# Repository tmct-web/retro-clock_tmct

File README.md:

# retro-clock_tmct
All discrete logic clock

This is a clock made by combining only logic ICs, so-called DIP components, without using a microcontroller.  
KiCad project files are available.

You can find more information on the following page. (*Japanese only)

[tmct web-site:nixie-clock](https://ss1.xrea.com/tmct.s1009.xrea.com/work/td-ja-7e4l01.html)

---
マイコンを使わず、いわゆるDIP部品のロジックICだけを組み合わせて作った時計です。  
KiCadのプロジェクトファイル一式を公開しています。

設計の仕様・組み立て方などの詳細は下記のページをご覧ください。

[tmct web-site:nixie-clock](https://ss1.xrea.com/tmct.s1009.xrea.com/work/td-ja-7e4l01.html)

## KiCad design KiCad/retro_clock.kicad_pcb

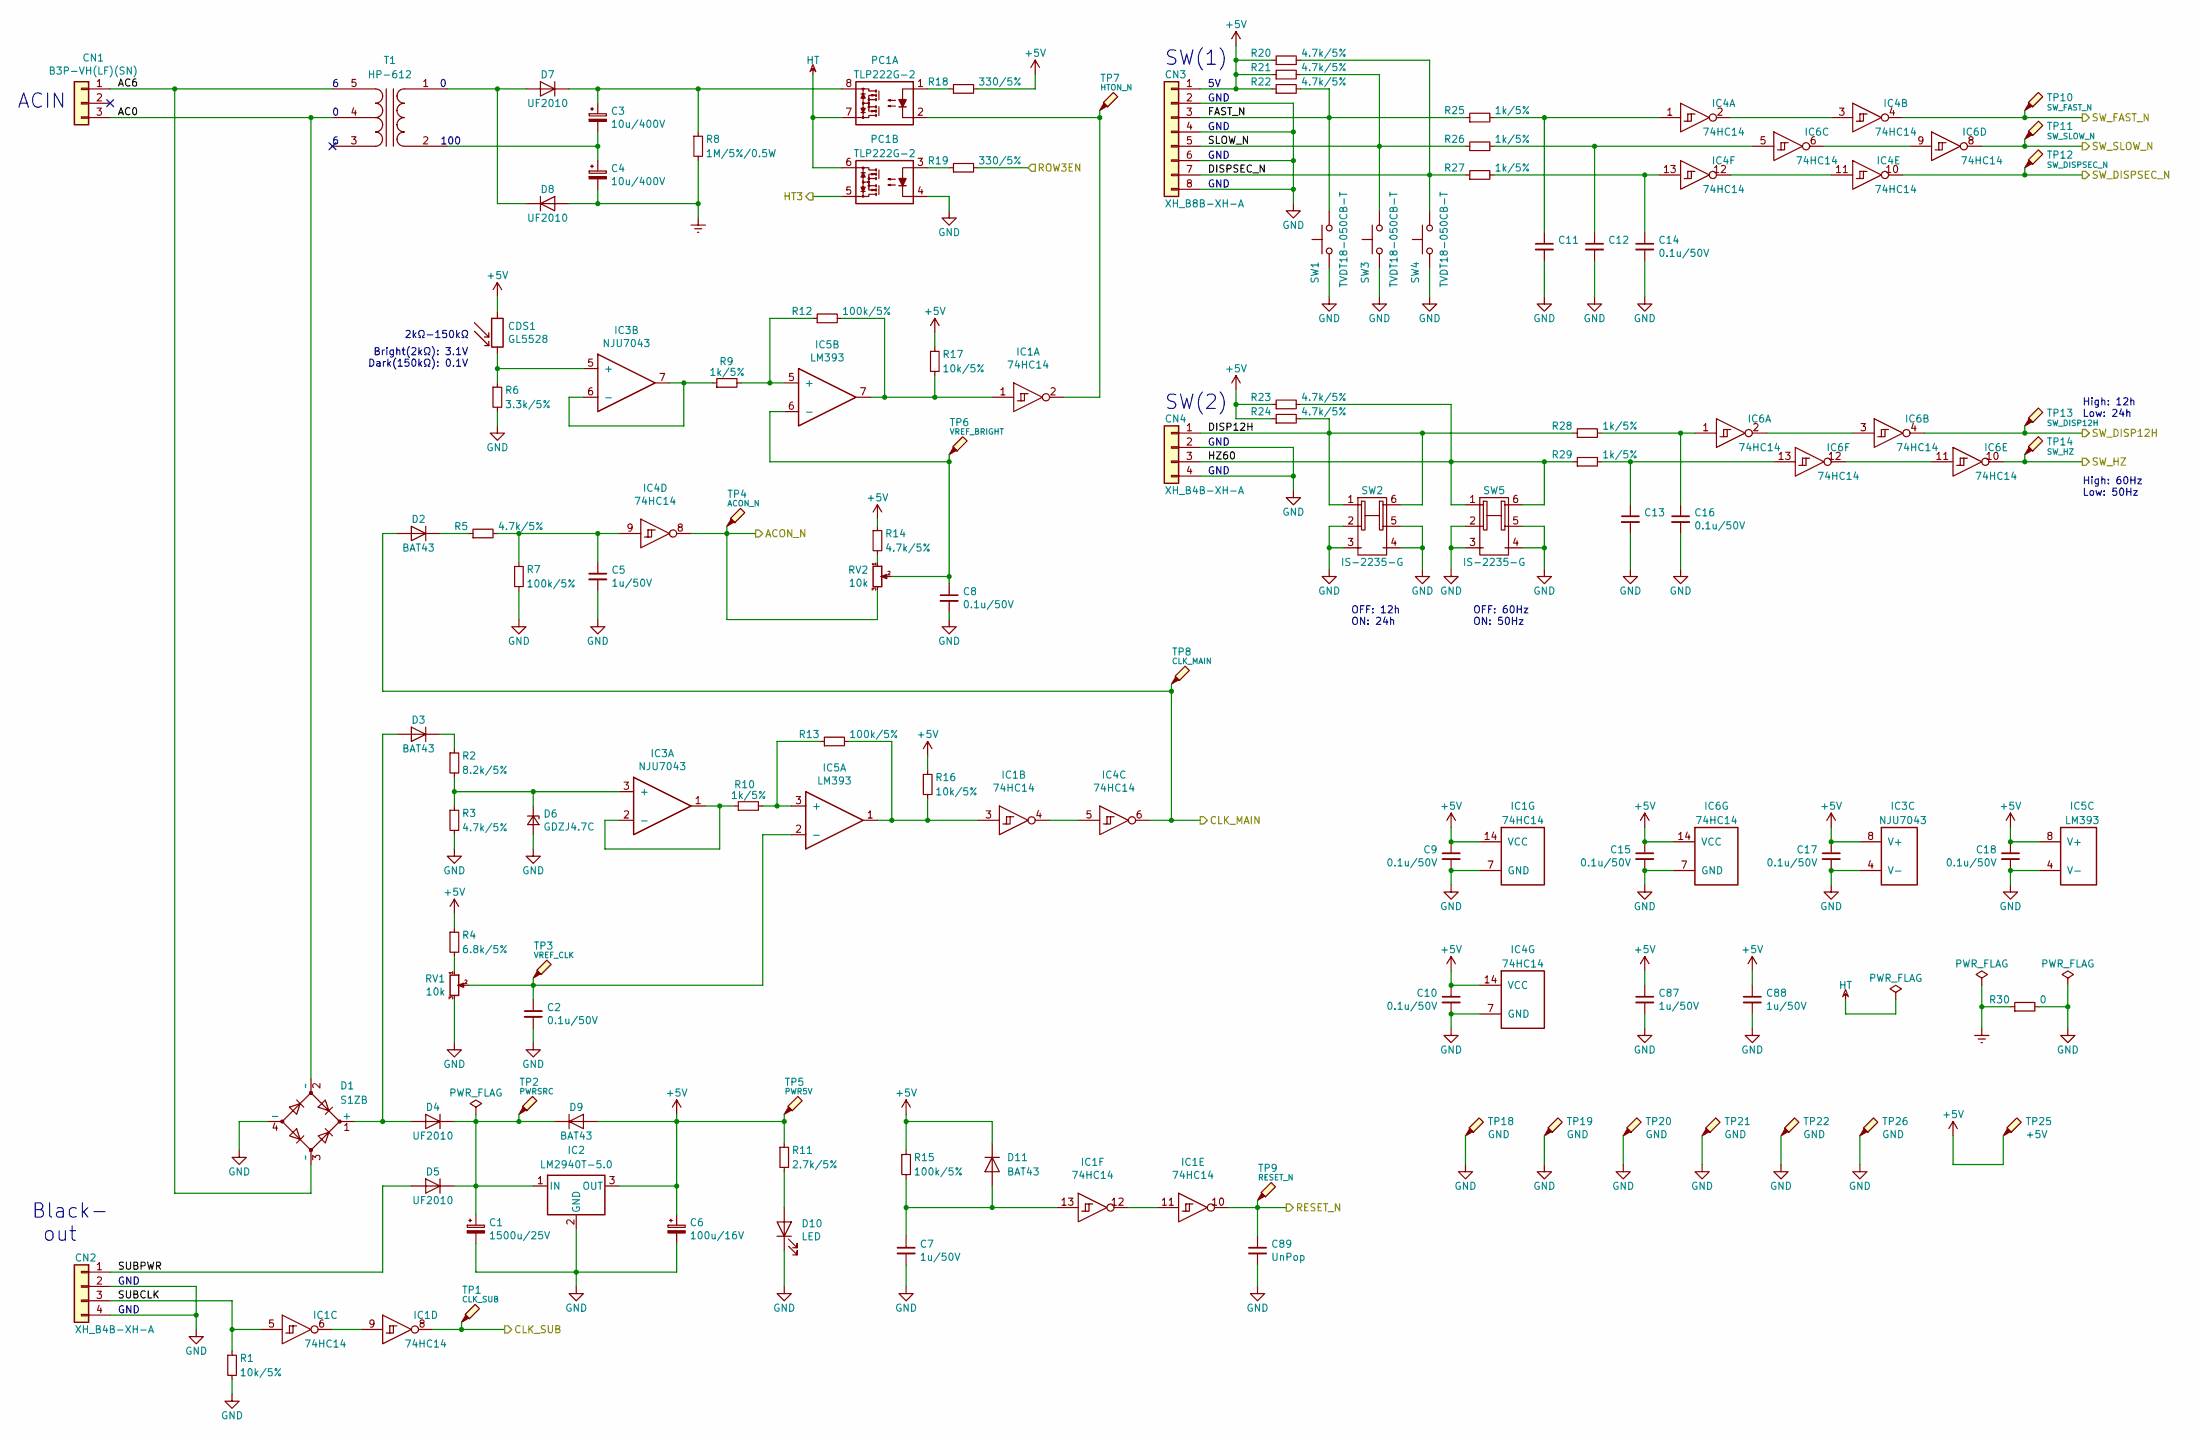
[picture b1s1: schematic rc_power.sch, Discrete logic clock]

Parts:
C1: 1500u/25V; CP_Radial_D12.5mm_P5.00mm
C2, C8, C9, C10, C11, C12, C13, C14, C15, C16, C17, C18: 0.1u/50V; C_Disc_P2.50mm
C3, C4: 10u/400V; CP_Radial_D12.5mm_P5.00mm
C5, C7, C87, C88: 1u/50V; C_Disc_P2.50mm
C6: 100u/16V; CP_Radial_D5.0mm_P2.00mm
C89: UnPop; C_Disc_P2.50mm
CDS1: GL5528; R_CDS_5.1x4.3mm_P3.4mm_Vertical
CN1: B3P-VH(LF)(SN); JST_VH_B3P-VH-B_1x03_P3.96mm_Vertical
CN2, CN4: XH_B4B-XH-A; JST_XH_B4B-XH-A_1x04_P2.50mm_Vertical
CN3: XH_B8B-XH-A; JST_XH_B8B-XH-A_1x08_P2.50mm_Vertical
D1: S1ZB; S1ZB-THD
D2, D3, D9, D11: BAT43; D_A-405_P7.62mm_Horizontal
D4, D5, D7, D8: UF2010; D_A-405_P10.16mm_Horizontal
D6: GDZJ4.7C; D_A-405_P7.62mm_Horizontal
D10: LED; LED_D3.0mm
IC1, IC4, IC6: 74HC14; DIP-14_W7.62mm_Socket_LongPads
IC2: LM2940T-5.0; TO-220-3_Vertical
IC3: NJU7043; DIP-8_W7.62mm_Socket_LongPads
IC5: LM393; DIP-8_W7.62mm_Socket_LongPads
PC1: TLP222G-2; DIP-8_W7.62mm_Socket_LongPads
R1, R16, R17: 10k/5%; R_Axial_P5.08mm_Horizontal
R2: 8.2k/5%; R_Axial_P5.08mm_Horizontal
R3, R5, R14, R20, R21, R22, R23, R24: 4.7k/5%; R_Axial_P5.08mm_Horizontal
R4: 6.8k/5%; R_Axial_P5.08mm_Horizontal
R6: 3.3k/5%; R_Axial_P5.08mm_Horizontal
R7, R12, R13, R15: 100k/5%; R_Axial_P5.08mm_Horizontal
R8: 1M/5%/0.5W; R_Axial_P7.62mm_Horizontal
R9, R10, R25, R26, R27, R28, R29: 1k/5%; R_Axial_P5.08mm_Horizontal
R11: 2.7k/5%; R_Axial_P5.08mm_Horizontal
R18, R19: 330/5%; R_Axial_P5.08mm_Horizontal
R30: 0; R_Axial_P5.08mm_Horizontal
RV1, RV2: 10k; Potentiometer_Bourns_3296W_Vertical
SW1, SW3, SW4: TVDT18-050CB-T
SW2, SW5: IS-2235-G
T1: HP-612; HP-098
TP1: CLK_SUB; TestPoint_THTPad_1.5x1.5mm_Drill0.7mm
TP2: PWRSRC; TestPoint_THTPad_1.5x1.5mm_Drill0.7mm
TP3: VREF_CLK; TestPoint_THTPad_1.5x1.5mm_Drill0.7mm
TP4: ACON_N; TestPoint_THTPad_1.5x1.5mm_Drill0.7mm
TP5: PWR5V; TestPoint_THTPad_1.5x1.5mm_Drill0.7mm
TP6: VREF_BRIGHT; TestPoint_THTPad_1.5x1.5mm_Drill0.7mm
TP7: HTON_N; TestPoint_THTPad_1.5x1.5mm_Drill0.7mm
TP8: CLK_MAIN; TestPoint_THTPad_1.5x1.5mm_Drill0.7mm
TP9: RESET_N; TestPoint_THTPad_1.5x1.5mm_Drill0.7mm
TP10: SW_FAST_N; TestPoint_THTPad_1.5x1.5mm_Drill0.7mm
TP11: SW_SLOW_N; TestPoint_THTPad_1.5x1.5mm_Drill0.7mm
TP12: SW_DISPSEC_N; TestPoint_THTPad_1.5x1.5mm_Drill0.7mm
TP13: SW_DISP12H; TestPoint_THTPad_1.5x1.5mm_Drill0.7mm
TP14: SW_HZ; TestPoint_THTPad_1.5x1.5mm_Drill0.7mm
TP18, TP19, TP20, TP21, TP22, TP26: GND; TestPoint_Loop_D2.60mm_Drill0.9mm_Beaded
TP25: +5V; TestPoint_Loop_D2.60mm_Drill0.9mm_Beaded

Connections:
+5V: C6.1, C9.1, C10.1, C15.1, C17.1, C18.1, C87.1, C88.1, CDS1.1, CN3.1, D9.2 (A), D11.1 (K), IC1.14 (VCC), IC2.3 (OUT), IC3.8 (V+), IC4.14 (VCC), IC5.8 (V+), IC6.14 (VCC), R4.1, R11.1, R14.1, R15.1, R16.1, R17.1, R18.2, R20.1, R21.1, R22.1, R23.1, R24.1, TP5.1, TP25.1; also elsewhere on the board
/Display block/HT3: PC1.5; also elsewhere on the board
/Divider block/ACON_N: IC4.8, RV2.3, TP4.1; also elsewhere on the board
/Divider block/CLK_MAIN: D2.2 (A), IC4.6, TP8.1; also elsewhere on the board
/Divider block/CLK_SUB: IC1.8, TP1.1; also elsewhere on the board
/Divider block/RESET_N: C89.1, IC1.10, TP9.1; also elsewhere on the board
/Divider block/SW_DISP12H: IC6.4, TP13.1; also elsewhere on the board
/Divider block/SW_DISPSEC_N: IC4.10, TP12.1; also elsewhere on the board
/Divider block/SW_FAST_N: IC4.4, TP10.1; also elsewhere on the board
/Divider block/SW_HZ: IC6.10, TP14.1; also elsewhere on the board
/Divider block/SW_SLOW_N: IC6.8, TP11.1; also elsewhere on the board
/Driver block/ROW3EN: R19.2; also elsewhere on the board
/Power block/AC0: CN1.3, D1.2 (~~), T1.4 (SC)
/Power block/AC6: CN1.1, D1.3 (~~), T1.5 (SB)
/Power block/DISP12H: CN4.1, R24.2, R28.1, SW2.1 (1a), SW2.6 (2a)
/Power block/DISPSEC_N: CN3.7, R20.2, R27.1, SW4.2
/Power block/FAST_N: CN3.3, R22.2, R25.1, SW1.2
/Power block/HZ60: CN4.3, R23.2, R29.1, SW5.1 (1a), SW5.6 (2a)
/Power block/SLOW_N: CN3.5, R21.2, R26.1, SW3.2
/Power block/SUBCLK: CN2.3, IC1.5, R1.1
/Power block/SUBPWR: CN2.1, D5.2 (A)
Earth: C4.2, D8.2 (A), R8.2, R30.1; also elsewhere on the board
GND: C1.2, C2.2, C5.2, C6.2, C7.2, C8.2, C9.2, C10.2, C11.2, C12.2, C13.2, C14.2, C15.2, C16.2, C17.2, C18.2, C87.2, C88.2, C89.2, CN2.2, CN2.4, CN3.2, CN3.4, CN3.6, CN3.8, CN4.2, CN4.4, D1.4 (-), D6.2 (A), D10.1 (K), IC1.7 (GND), IC2.2 (GND), IC3.4 (V-), IC4.7 (GND), IC5.4 (V-), IC6.7 (GND), PC1.4, R1.2, R3.2, R6.2, R7.2, R30.2, RV1.3, SW1.1, SW2.2 (1c), SW2.3 (1b), SW2.4 (2b), SW2.5 (2c), SW3.1, SW4.1, SW5.2 (1c), SW5.3 (1b), SW5.4 (2b), SW5.5 (2c), TP18.1, TP19.1, TP20.1, TP21.1, TP22.1, TP26.1; also elsewhere on the board
HT: PC1.6, PC1.7; also elsewhere on the board
unnamed: C1.1, D4.1 (K), D5.1 (K), D9.1 (K), IC2.1 (IN), TP2.1
unnamed: C2.1, IC5.2 (-), RV1.2, TP3.1
unnamed: C3.1, D7.1 (K), PC1.8, R8.1
unnamed: C3.2, C4.1, T1.2 (AB)
unnamed: C5.1, IC4.9, R5.2, R7.1
unnamed: C7.1, D11.2 (A), IC1.13, R15.2
unnamed: C8.1, IC5.6 (-), RV2.2, TP6.1
unnamed: C11.1, IC4.1, R25.2
unnamed: C12.1, IC6.5, R26.2
unnamed: C13.1, IC6.13, R29.2
unnamed: C14.1, IC4.13, R27.2
unnamed: C16.1, IC6.1, R28.2
unnamed: CDS1.2, IC3.5 (+), R6.1
unnamed: D1.1 (+), D3.2 (A), D4.2 (A)
unnamed: D2.1 (K), R5.1
unnamed: D3.1 (K), R2.1
unnamed: D6.1 (K), IC3.3 (+), R2.2, R3.1
unnamed: D7.2 (A), D8.1 (K), T1.1 (AA)
unnamed: D10.2 (A), R11.2
unnamed: IC1.1, IC5.7, R12.2, R17.2
unnamed: IC1.2, PC1.2, TP7.1
unnamed: IC1.3, IC5.1, R13.2, R16.2
unnamed: IC1.4, IC4.5
unnamed: IC1.6, IC1.9
unnamed: IC1.11, IC1.12
unnamed: IC3.1, IC3.2 (-), R10.1
unnamed: IC3.6 (-), IC3.7, R9.1
unnamed: IC4.2, IC4.3
unnamed: IC4.11, IC4.12
unnamed: IC5.3 (+), R10.2, R13.1
unnamed: IC5.5 (+), R9.2, R12.1
unnamed: IC6.2, IC6.3
unnamed: IC6.6, IC6.9
unnamed: IC6.11, IC6.12
unnamed: PC1.1, R18.1
unnamed: PC1.3, R19.1
unnamed: R4.2, RV1.1
unnamed: R14.2, RV2.1

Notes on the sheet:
ACIN
SW(1)
2kΩ-150kΩ
Bright(2kΩ): 3.1V Dark(150kΩ): 0.1V
SW(2)
Black- out
GND
100
High: 60Hz Low: 50Hz
High: 12h Low: 24h
OFF: 60Hz ON: 50Hz
OFF: 12h ON: 24h

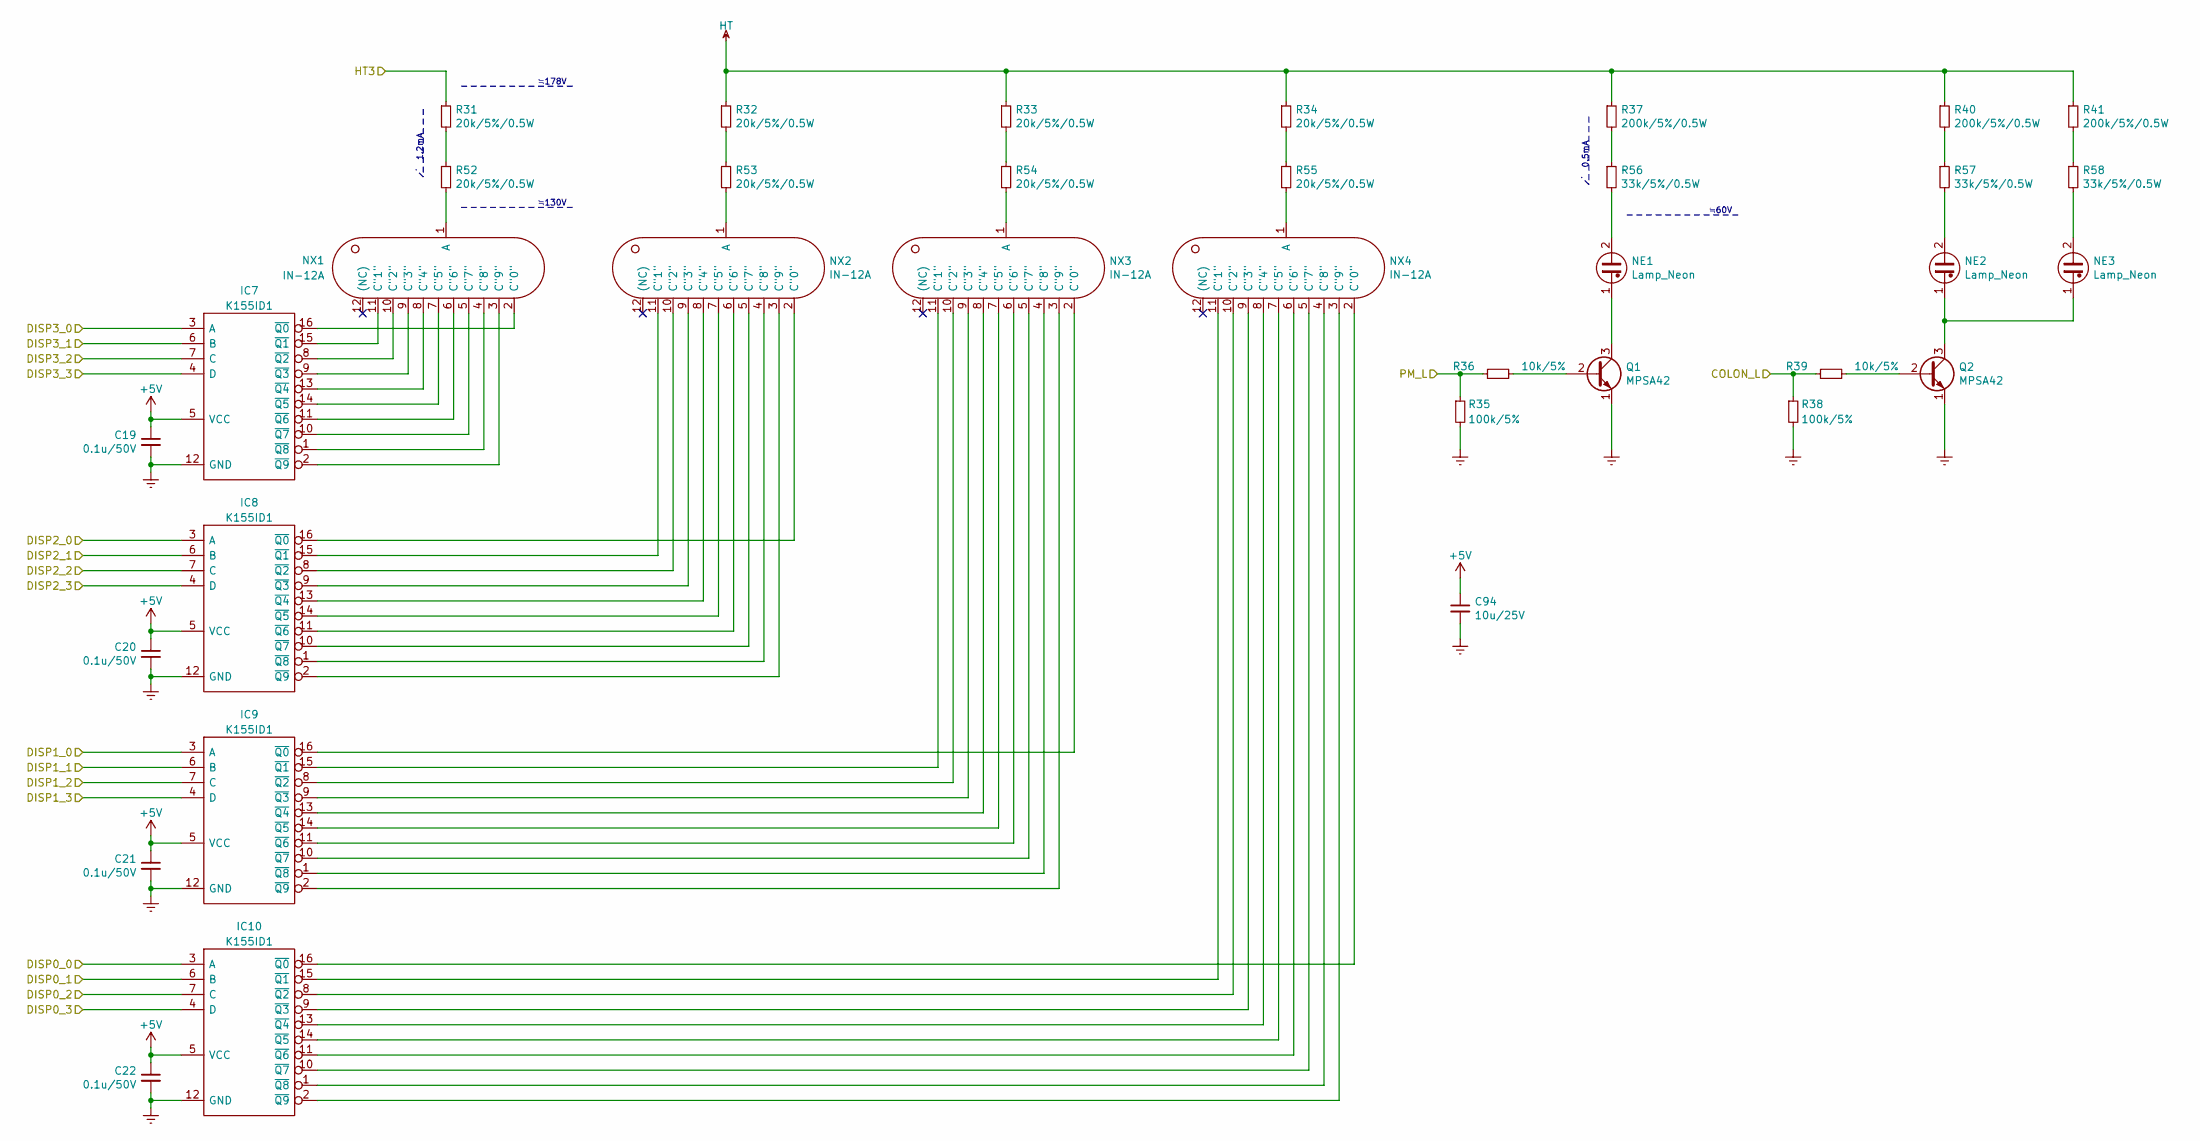
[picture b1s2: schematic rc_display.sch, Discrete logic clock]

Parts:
C19, C20, C21, C22: 0.1u/50V; C_Disc_P2.50mm
C94: 10u/25V; C_Disc_P5.00mm
IC7, IC8, IC9, IC10: K155ID1; DIP-16_W7.62mm_Socket_LongPads
NE1, NE2, NE3: Lamp_Neon; NeonLamp
NX1, NX2, NX3, NX4: IN-12A; IN-12
Q1, Q2: MPSA42; TO-92_HandSolder
R31, R32, R33, R34, R52, R53, R54, R55: 20k/5%/0.5W; R_Axial_P7.62mm_Horizontal
R35, R38: 100k/5%; R_Axial_P5.08mm_Horizontal
R36, R39: 10k/5%; R_Axial_P5.08mm_Horizontal
R37, R40, R41: 200k/5%/0.5W; R_Axial_P7.62mm_Horizontal
R56, R57, R58: 33k/5%/0.5W; R_Axial_P7.62mm_Horizontal

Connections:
+5V: C19.1, C20.1, C21.1, C22.1, C94.1, IC7.5 (VCC), IC8.5 (VCC), IC9.5 (VCC), IC10.5 (VCC); also elsewhere on the board
/Display block/COLON_L: R38.1, R39.1; also elsewhere on the board
/Display block/DISP0_0: IC10.3 (A); also elsewhere on the board
/Display block/DISP0_1: IC10.6 (B); also elsewhere on the board
/Display block/DISP0_2: IC10.7 (C); also elsewhere on the board
/Display block/DISP0_3: IC10.4 (D); also elsewhere on the board
/Display block/DISP1_0: IC9.3 (A); also elsewhere on the board
/Display block/DISP1_1: IC9.6 (B); also elsewhere on the board
/Display block/DISP1_2: IC9.7 (C); also elsewhere on the board
/Display block/DISP1_3: IC9.4 (D); also elsewhere on the board
/Display block/DISP2_0: IC8.3 (A); also elsewhere on the board
/Display block/DISP2_1: IC8.6 (B); also elsewhere on the board
/Display block/DISP2_2: IC8.7 (C); also elsewhere on the board
/Display block/DISP2_3: IC8.4 (D); also elsewhere on the board
/Display block/DISP3_0: IC7.3 (A); also elsewhere on the board
/Display block/DISP3_1: IC7.6 (B); also elsewhere on the board
/Display block/DISP3_2: IC7.7 (C); also elsewhere on the board
/Display block/DISP3_3: IC7.4 (D); also elsewhere on the board
/Display block/HT3: R31.1; also elsewhere on the board
/Display block/PM_L: R35.1, R36.1; also elsewhere on the board
Earth: C19.2, C20.2, C21.2, C22.2, C94.2, IC7.12 (GND), IC8.12 (GND), IC9.12 (GND), IC10.12 (GND), Q1.1 (E), Q2.1 (E), R35.2, R38.2; also elsewhere on the board
HT: R32.1, R33.1, R34.1, R37.1, R40.1, R41.1; also elsewhere on the board
unnamed: IC7.1 (~Q8), NX1.4 (C"8")
unnamed: IC7.2 (~Q9), NX1.3 (C"9")
unnamed: IC7.8 (~Q2), NX1.10 (C"2")
unnamed: IC7.9 (~Q3), NX1.9 (C"3")
unnamed: IC7.10 (~Q7), NX1.5 (C"7")
unnamed: IC7.11 (~Q6), NX1.6 (C"6")
unnamed: IC7.13 (~Q4), NX1.8 (C"4")
unnamed: IC7.14 (~Q5), NX1.7 (C"5")
unnamed: IC7.15 (~Q1), NX1.11 (C"1")
unnamed: IC7.16 (~Q0), NX1.2 (C"0")
unnamed: IC8.1 (~Q8), NX2.4 (C"8")
unnamed: IC8.2 (~Q9), NX2.3 (C"9")
unnamed: IC8.8 (~Q2), NX2.10 (C"2")
unnamed: IC8.9 (~Q3), NX2.9 (C"3")
unnamed: IC8.10 (~Q7), NX2.5 (C"7")
unnamed: IC8.11 (~Q6), NX2.6 (C"6")
unnamed: IC8.13 (~Q4), NX2.8 (C"4")
unnamed: IC8.14 (~Q5), NX2.7 (C"5")
unnamed: IC8.15 (~Q1), NX2.11 (C"1")
unnamed: IC8.16 (~Q0), NX2.2 (C"0")
unnamed: IC9.1 (~Q8), NX3.4 (C"8")
unnamed: IC9.2 (~Q9), NX3.3 (C"9")
unnamed: IC9.8 (~Q2), NX3.10 (C"2")
unnamed: IC9.9 (~Q3), NX3.9 (C"3")
unnamed: IC9.10 (~Q7), NX3.5 (C"7")
unnamed: IC9.11 (~Q6), NX3.6 (C"6")
unnamed: IC9.13 (~Q4), NX3.8 (C"4")
unnamed: IC9.14 (~Q5), NX3.7 (C"5")
unnamed: IC9.15 (~Q1), NX3.11 (C"1")
unnamed: IC9.16 (~Q0), NX3.2 (C"0")
unnamed: IC10.1 (~Q8), NX4.4 (C"8")
unnamed: IC10.2 (~Q9), NX4.3 (C"9")
unnamed: IC10.8 (~Q2), NX4.10 (C"2")
unnamed: IC10.9 (~Q3), NX4.9 (C"3")
unnamed: IC10.10 (~Q7), NX4.5 (C"7")
unnamed: IC10.11 (~Q6), NX4.6 (C"6")
unnamed: IC10.13 (~Q4), NX4.8 (C"4")
unnamed: IC10.14 (~Q5), NX4.7 (C"5")
unnamed: IC10.15 (~Q1), NX4.11 (C"1")
unnamed: IC10.16 (~Q0), NX4.2 (C"0")
unnamed: NE1.1, Q1.3 (C)
unnamed: NE1.2, R56.2
unnamed: NE2.1, NE3.1, Q2.3 (C)
unnamed: NE2.2, R57.2
unnamed: NE3.2, R58.2
unnamed: NX1.1 (A), R52.2
unnamed: NX2.1 (A), R53.2
unnamed: NX3.1 (A), R54.2
unnamed: NX4.1 (A), R55.2
unnamed: Q1.2 (B), R36.2
unnamed: Q2.2 (B), R39.2
unnamed: R31.2, R52.1
unnamed: R32.2, R53.1
unnamed: R33.2, R54.1
unnamed: R34.2, R55.1
unnamed: R37.2, R56.1
unnamed: R40.2, R57.1
unnamed: R41.2, R58.1

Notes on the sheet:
1.2mA
≒178V
≒130V
0.5mA
≒60V

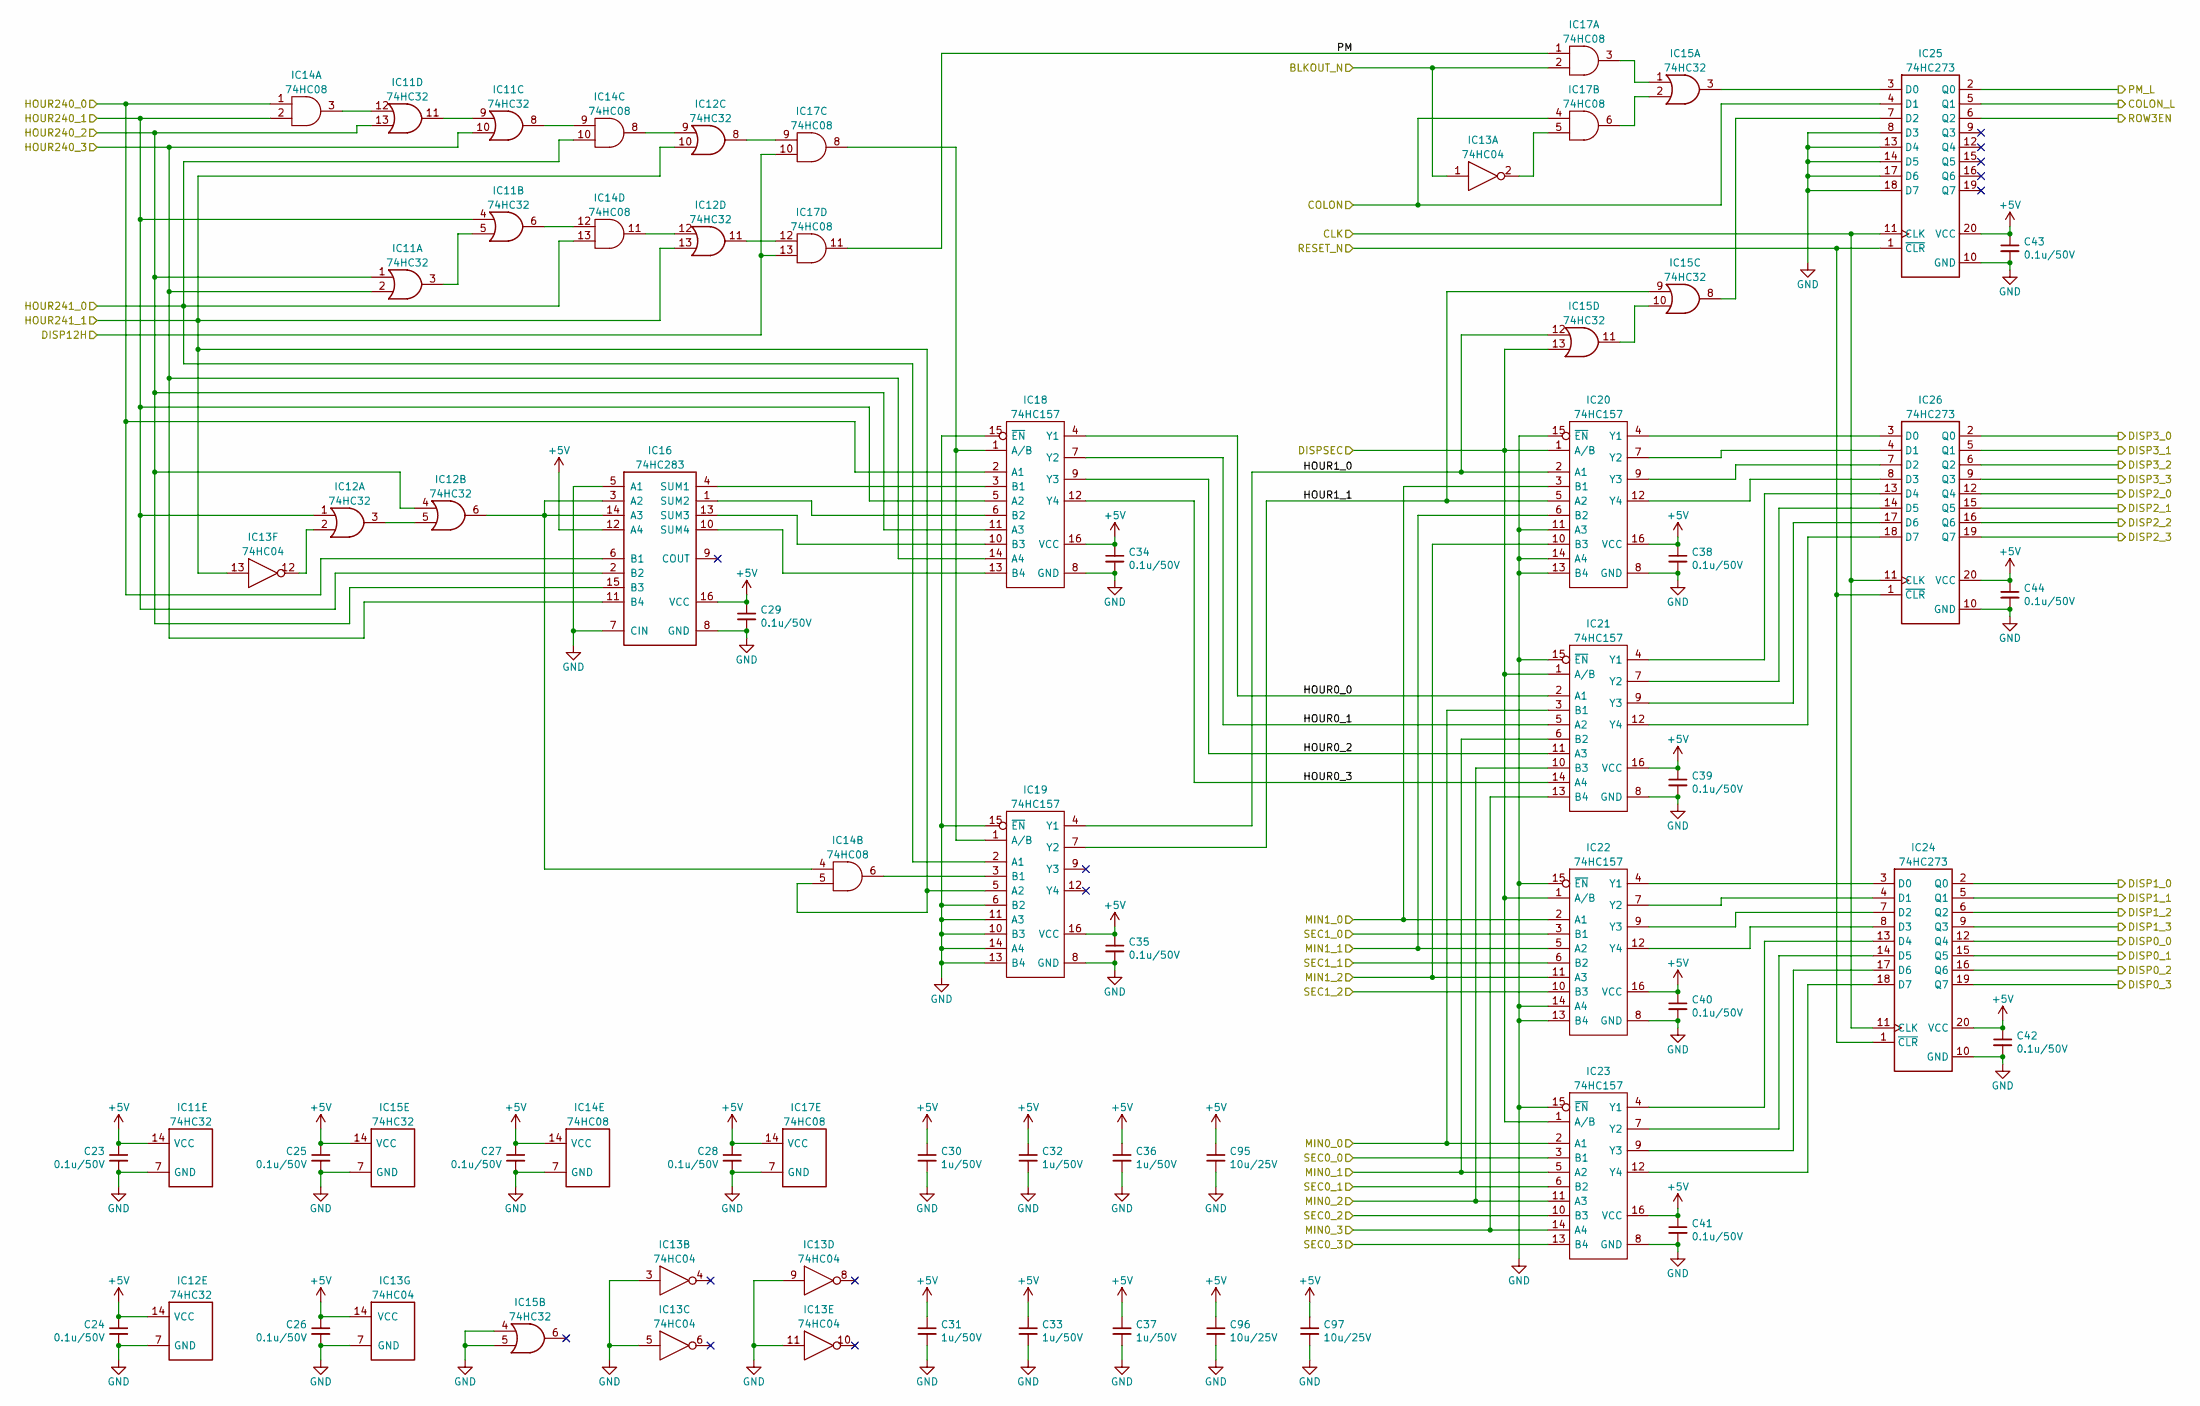
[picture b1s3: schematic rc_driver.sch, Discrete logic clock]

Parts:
C23, C24, C25, C26, C27, C28, C29, C34, C35, C38, C39, C40, C41, C42, C43, C44: 0.1u/50V; C_Disc_P2.50mm
C30, C31, C32, C33, C36, C37: 1u/50V; C_Disc_P2.50mm
C95, C96, C97: 10u/25V; C_Disc_P5.00mm
IC11, IC12, IC15: 74HC32; DIP-14_W7.62mm_Socket_LongPads
IC13: 74HC04; DIP-14_W7.62mm_Socket_LongPads
IC14, IC17: 74HC08; DIP-14_W7.62mm_Socket_LongPads
IC16: 74HC283; DIP-16_W7.62mm_Socket_LongPads
IC18, IC19, IC20, IC21, IC22, IC23: 74HC157; DIP-16_W7.62mm_Socket_LongPads
IC24, IC25, IC26: 74HC273; DIP-20_W7.62mm_Socket_LongPads

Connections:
+5V: C23.1, C24.1, C25.1, C26.1, C27.1, C28.1, C29.1, C30.1, C31.1, C32.1, C33.1, C34.1, C35.1, C36.1, C37.1, C38.1, C39.1, C40.1, C41.1, C42.1, C43.1, C44.1, C95.1, C96.1, C97.1, IC11.14 (VCC), IC12.14 (VCC), IC13.14 (VCC), IC14.14 (VCC), IC15.14 (VCC), IC16.12 (A4), IC16.16 (VCC), IC17.14 (VCC), IC18.16 (VCC), IC19.16 (VCC), IC20.16 (VCC), IC21.16 (VCC), IC22.16 (VCC), IC23.16 (VCC), IC24.20 (VCC), IC25.20 (VCC), IC26.20 (VCC); also elsewhere on the board
/Display block/COLON_L: IC25.5 (Q1); also elsewhere on the board
/Display block/DISP0_0: IC24.12 (Q4); also elsewhere on the board
/Display block/DISP0_1: IC24.15 (Q5); also elsewhere on the board
/Display block/DISP0_2: IC24.16 (Q6); also elsewhere on the board
/Display block/DISP0_3: IC24.19 (Q7); also elsewhere on the board
/Display block/DISP1_0: IC24.2 (Q0); also elsewhere on the board
/Display block/DISP1_1: IC24.5 (Q1); also elsewhere on the board
/Display block/DISP1_2: IC24.6 (Q2); also elsewhere on the board
/Display block/DISP1_3: IC24.9 (Q3); also elsewhere on the board
/Display block/DISP2_0: IC26.12 (Q4); also elsewhere on the board
/Display block/DISP2_1: IC26.15 (Q5); also elsewhere on the board
/Display block/DISP2_2: IC26.16 (Q6); also elsewhere on the board
/Display block/DISP2_3: IC26.19 (Q7); also elsewhere on the board
/Display block/DISP3_0: IC26.2 (Q0); also elsewhere on the board
/Display block/DISP3_1: IC26.5 (Q1); also elsewhere on the board
/Display block/DISP3_2: IC26.6 (Q2); also elsewhere on the board
/Display block/DISP3_3: IC26.9 (Q3); also elsewhere on the board
/Display block/PM_L: IC25.2 (Q0); also elsewhere on the board
/Divider block/BLKOUT_N: IC13.1, IC17.2; also elsewhere on the board
/Divider block/COLON: IC17.4, IC25.4 (D1); also elsewhere on the board
/Divider block/DISP12H: IC17.10, IC17.13; also elsewhere on the board
/Divider block/DISPSEC: IC15.13, IC20.1 (A/B), IC21.1 (A/B), IC22.1 (A/B), IC23.1 (A/B); also elsewhere on the board
/Divider block/RESET_DRV_N: IC24.1 (~CLR), IC25.1 (~CLR), IC26.1 (~CLR); also elsewhere on the board
/Driver block/CLK: IC24.11 (CLK), IC25.11 (CLK), IC26.11 (CLK); also elsewhere on the board
/Driver block/HOUR0_0: IC18.4 (Y1), IC21.2 (A1)
/Driver block/HOUR0_1: IC18.7 (Y2), IC21.5 (A2)
/Driver block/HOUR0_2: IC18.9 (Y3), IC21.11 (A3)
/Driver block/HOUR0_3: IC18.12 (Y4), IC21.14 (A4)
/Driver block/HOUR1_0: IC15.12, IC19.4 (Y1), IC20.2 (A1)
/Driver block/HOUR1_1: IC15.9, IC19.7 (Y2), IC20.5 (A2)
/Driver block/HOUR240_0: IC14.1, IC16.6 (B1), IC18.2 (A1); also elsewhere on the board
/Driver block/HOUR240_1: IC11.4, IC12.1, IC14.2, IC16.2 (B2), IC18.5 (A2); also elsewhere on the board
/Driver block/HOUR240_2: IC11.1, IC11.13, IC12.4, IC16.15 (B3), IC18.11 (A3); also elsewhere on the board
/Driver block/HOUR240_3: IC11.2, IC11.10, IC16.11 (B4), IC18.14 (A4); also elsewhere on the board
/Driver block/HOUR241_0: IC14.10, IC14.13, IC19.2 (A1); also elsewhere on the board
/Driver block/HOUR241_1: IC12.10, IC12.13, IC13.13, IC14.5, IC19.5 (A2); also elsewhere on the board
/Driver block/MIN0_0: IC21.3 (B1), IC23.2 (A1); also elsewhere on the board
/Driver block/MIN0_1: IC21.6 (B2), IC23.5 (A2); also elsewhere on the board
/Driver block/MIN0_2: IC21.10 (B3), IC23.11 (A3); also elsewhere on the board
/Driver block/MIN0_3: IC21.13 (B4), IC23.14 (A4); also elsewhere on the board
/Driver block/MIN1_0: IC20.3 (B1), IC22.2 (A1); also elsewhere on the board
/Driver block/MIN1_1: IC20.6 (B2), IC22.5 (A2); also elsewhere on the board
/Driver block/MIN1_2: IC20.10 (B3), IC22.11 (A3); also elsewhere on the board
/Driver block/PM: IC17.1, IC17.11
/Driver block/ROW3EN: IC25.6 (Q2); also elsewhere on the board
/Driver block/SEC0_0: IC23.3 (B1); also elsewhere on the board
/Driver block/SEC0_1: IC23.6 (B2); also elsewhere on the board
/Driver block/SEC0_2: IC23.10 (B3); also elsewhere on the board
/Driver block/SEC0_3: IC23.13 (B4); also elsewhere on the board
/Driver block/SEC1_0: IC22.3 (B1); also elsewhere on the board
/Driver block/SEC1_1: IC22.6 (B2); also elsewhere on the board
/Driver block/SEC1_2: IC22.10 (B3); also elsewhere on the board
GND: C23.2, C24.2, C25.2, C26.2, C27.2, C28.2, C29.2, C30.2, C31.2, C32.2, C33.2, C34.2, C35.2, C36.2, C37.2, C38.2, C39.2, C40.2, C41.2, C42.2, C43.2, C44.2, C95.2, C96.2, C97.2, IC11.7 (GND), IC12.7 (GND), IC13.3, IC13.5, IC13.7 (GND), IC13.9, IC13.11, IC14.7 (GND), IC15.4, IC15.5, IC15.7 (GND), IC16.5 (A1), IC16.7 (CIN), IC16.8 (GND), IC17.7 (GND), IC18.8 (GND), IC18.15 (~EN), IC19.6 (B2), IC19.8 (GND), IC19.10 (B3), IC19.11 (A3), IC19.13 (B4), IC19.14 (A4), IC19.15 (~EN), IC20.8 (GND), IC20.11 (A3), IC20.13 (B4), IC20.14 (A4), IC20.15 (~EN), IC21.8 (GND), IC21.15 (~EN), IC22.8 (GND), IC22.13 (B4), IC22.14 (A4), IC22.15 (~EN), IC23.8 (GND), IC23.15 (~EN), IC24.10 (GND), IC25.8 (D3), IC25.10 (GND), IC25.13 (D4), IC25.14 (D5), IC25.17 (D6), IC25.18 (D7), IC26.10 (GND); also elsewhere on the board
unnamed: IC11.3, IC11.5
unnamed: IC11.6, IC14.12
unnamed: IC11.8, IC14.9
unnamed: IC11.9, IC11.11
unnamed: IC11.12, IC14.3
unnamed: IC12.2, IC13.12
unnamed: IC12.3, IC12.5
unnamed: IC12.6, IC14.4, IC16.3 (A2), IC16.14 (A3)
unnamed: IC12.8, IC17.9
unnamed: IC12.9, IC14.8
unnamed: IC12.11, IC17.12
unnamed: IC12.12, IC14.11
unnamed: IC13.2, IC17.5
unnamed: IC14.6, IC19.3 (B1)
unnamed: IC15.1, IC17.3
unnamed: IC15.2, IC17.6
unnamed: IC15.3, IC25.3 (D0)
unnamed: IC15.8, IC25.7 (D2)
unnamed: IC15.10, IC15.11
unnamed: IC16.1 (SUM2), IC18.6 (B2)
unnamed: IC16.4 (SUM1), IC18.3 (B1)
unnamed: IC16.10 (SUM4), IC18.13 (B4)
unnamed: IC16.13 (SUM3), IC18.10 (B3)
unnamed: IC17.8, IC18.1 (A/B), IC19.1 (A/B)
unnamed: IC20.4 (Y1), IC26.3 (D0)
unnamed: IC20.7 (Y2), IC26.4 (D1)
unnamed: IC20.9 (Y3), IC26.7 (D2)
unnamed: IC20.12 (Y4), IC26.8 (D3)
unnamed: IC21.4 (Y1), IC26.13 (D4)
unnamed: IC21.7 (Y2), IC26.14 (D5)
unnamed: IC21.9 (Y3), IC26.17 (D6)
unnamed: IC21.12 (Y4), IC26.18 (D7)
unnamed: IC22.4 (Y1), IC24.3 (D0)
unnamed: IC22.7 (Y2), IC24.4 (D1)
unnamed: IC22.9 (Y3), IC24.7 (D2)
unnamed: IC22.12 (Y4), IC24.8 (D3)
unnamed: IC23.4 (Y1), IC24.13 (D4)
unnamed: IC23.7 (Y2), IC24.14 (D5)
unnamed: IC23.9 (Y3), IC24.17 (D6)
unnamed: IC23.12 (Y4), IC24.18 (D7)

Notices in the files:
KiCad/rc_display.sch:
© 2020 tmct All Rights Reserved.
